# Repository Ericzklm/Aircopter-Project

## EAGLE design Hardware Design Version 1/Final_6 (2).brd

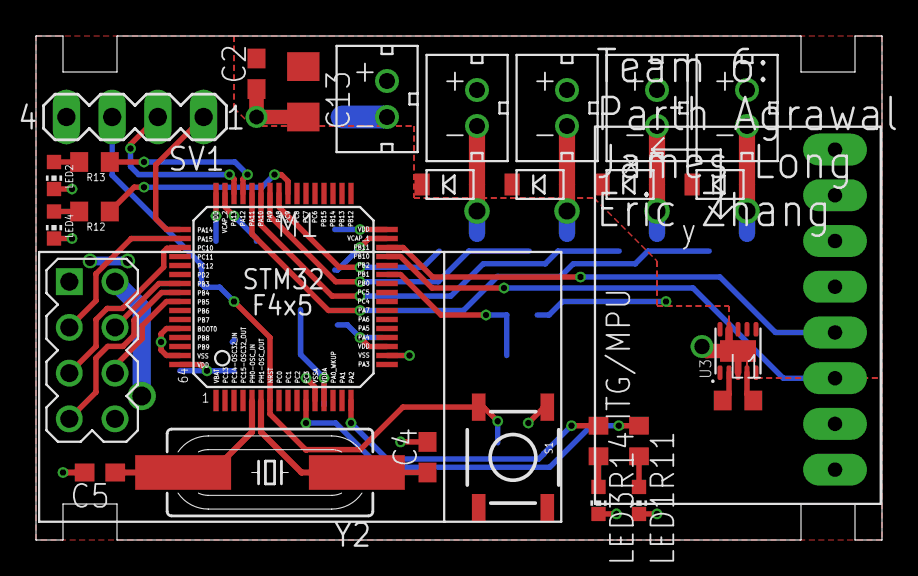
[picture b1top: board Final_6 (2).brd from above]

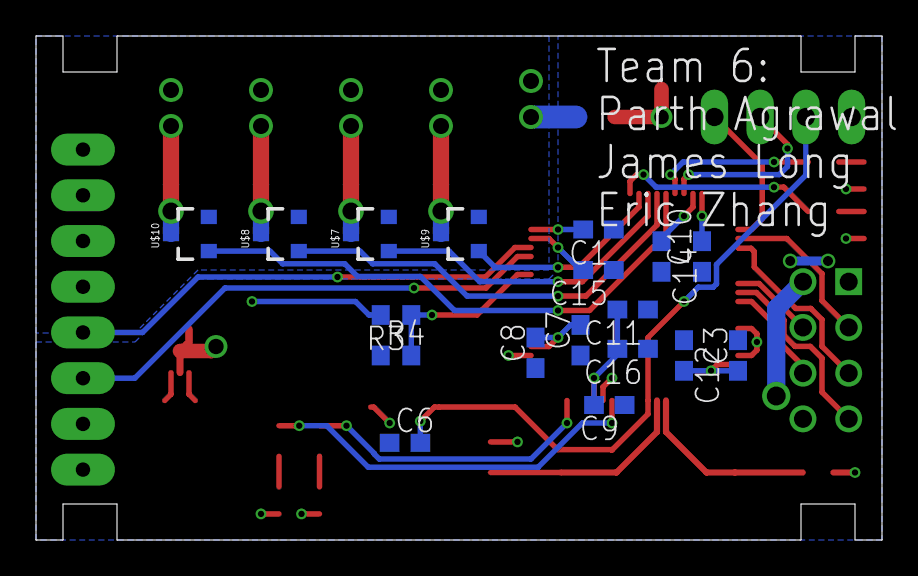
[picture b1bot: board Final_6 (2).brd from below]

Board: 2 copper layers, 47.0 x 28.0 mm, 47 parts (18 on the bottom side), 36 nets.

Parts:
C1, C7, C9, C10, C11, C12: 100nF; C0603
C2, C8: 10uF; C0603
C3: 22uF; C0603
C4, C5: 16pF; C0603
C6: 1uF; C0603
C13: 100uF; C1206
C14, C15: 2.2uF; C0603
C16: 4.7uF; C0603
L1: 2.2uH; L0603
LED1, LED4: Blue; CHIP-LED0603
LED2, LED3: Green; CHIP-LED0603
M1: WIRELESS-NRF24L01
R3, R4: 10k; R0603
R11, R12, R13, R14: 300; R0603
S1: SWITCH-MOMENTARY-2SMD; TACTILE-SWITCH-SMD
SV1: MA04-1
U2: GY-521MPU6050; GY-521
U3: RT6150B-33GQW; SON50P250X250X80-11N
U$1: STM32F405/415_LQFP64
U$2, U$3, U$4, U$5, U$6: JST_CONNECTOR_FEMALE
U$7, U$8, U$9, U$10: N-CHANNEL-MOSFET-IRLML6244TRPBF; SOT23-3
U$11, U$12, U$13, U$14: DB2W40300L; MINI2-F3-B
Y2: 12MHz; HC49UP

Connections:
3.7V: C2.2, C13.1, R3.2, U3.5, U3.6, U3.7, U3.8, U$2.+, U$3.+, U$4.+, U$5.+, U$6.+, U$11.NEG, U$12.NEG, U$13.NEG, U$14.NEG
ANALOG: R3.1, R4.2, U$1.PB1
CE: M1.3, U$1.PA15
CSN: M1.4, U$1.PB3
GND: C1.1, C2.1, C3.2, C4.2, C5.2, C6.1, C7.1, C8.1, C9.1, C10.1, C11.1, C12.1, C13.2, C14.2, C15.1, C16.1, LED1.C, LED2.C, LED3.C, LED4.C, M1.1, R4.1, S1.1, SV1.4, U2.GND, U3.3, U3.9, U3.11, U$1.BOOT0, U$1.VSSA, U$1.VSS_0, U$1.VSS_1, U$2.-, U$7.2, U$8.2, U$9.2, U$10.2
LED_MISO: R14.1, U$1.PA2
LED_PWR: R11.1, U$1.PC3
LED_RST: R12.1, U$1.PC9
LED_SWDIO: R13.1, U$1.PA12
MISO: M1.7, U$1.PB4
MOSI: M1.6, U$1.PB5
unnamed: L1.2, U3.4
unnamed: L1.1, U3.2
unnamed: U$3.-, U$9.3, U$11.POS
unnamed: U$5.-, U$8.3, U$12.POS
unnamed: U$4.-, U$7.3, U$13.POS
unnamed: U$6.-, U$10.3, U$14.POS
unnamed: LED1.A, R11.2
unnamed: LED4.A, R12.2
unnamed: LED2.A, R13.2
unnamed: LED3.A, R14.2
unnamed: C15.2, U$1.VCAP_1
unnamed: C14.1, U$1.VCAP_2
OSC_IN: C5.1, U$1.PH0, Y2.2
OSC_OUT: C4.1, U$1.PH1, Y2.1
RESET: C6.2, S1.3, SV1.3, U$1.NRST
SCK: M1.5, U$1.PC10
SCL: U2.SCL, U$1.PB10
SDA: U2.SDA, U$1.PB11
SWCLK: SV1.1, U$1.PA14
SWDIO: SV1.2, U$1.PA13
TIM1: U$1.PA11, U$10.1
TIM2: U$1.PA10, U$8.1
TIM3: U$1.PA9, U$7.1
TIM4: U$1.PA8, U$9.1
VOUT: C1.2, C3.1, C7.2, C8.2, C9.2, C10.2, C11.2, C12.2, C16.2, M1.2, U2.VCC, U3.1, U3.10, U$1.VDDA, U$1.VDD_0, U$1.VDD_1, U$1.VDD_2, U$1.VDD_3
